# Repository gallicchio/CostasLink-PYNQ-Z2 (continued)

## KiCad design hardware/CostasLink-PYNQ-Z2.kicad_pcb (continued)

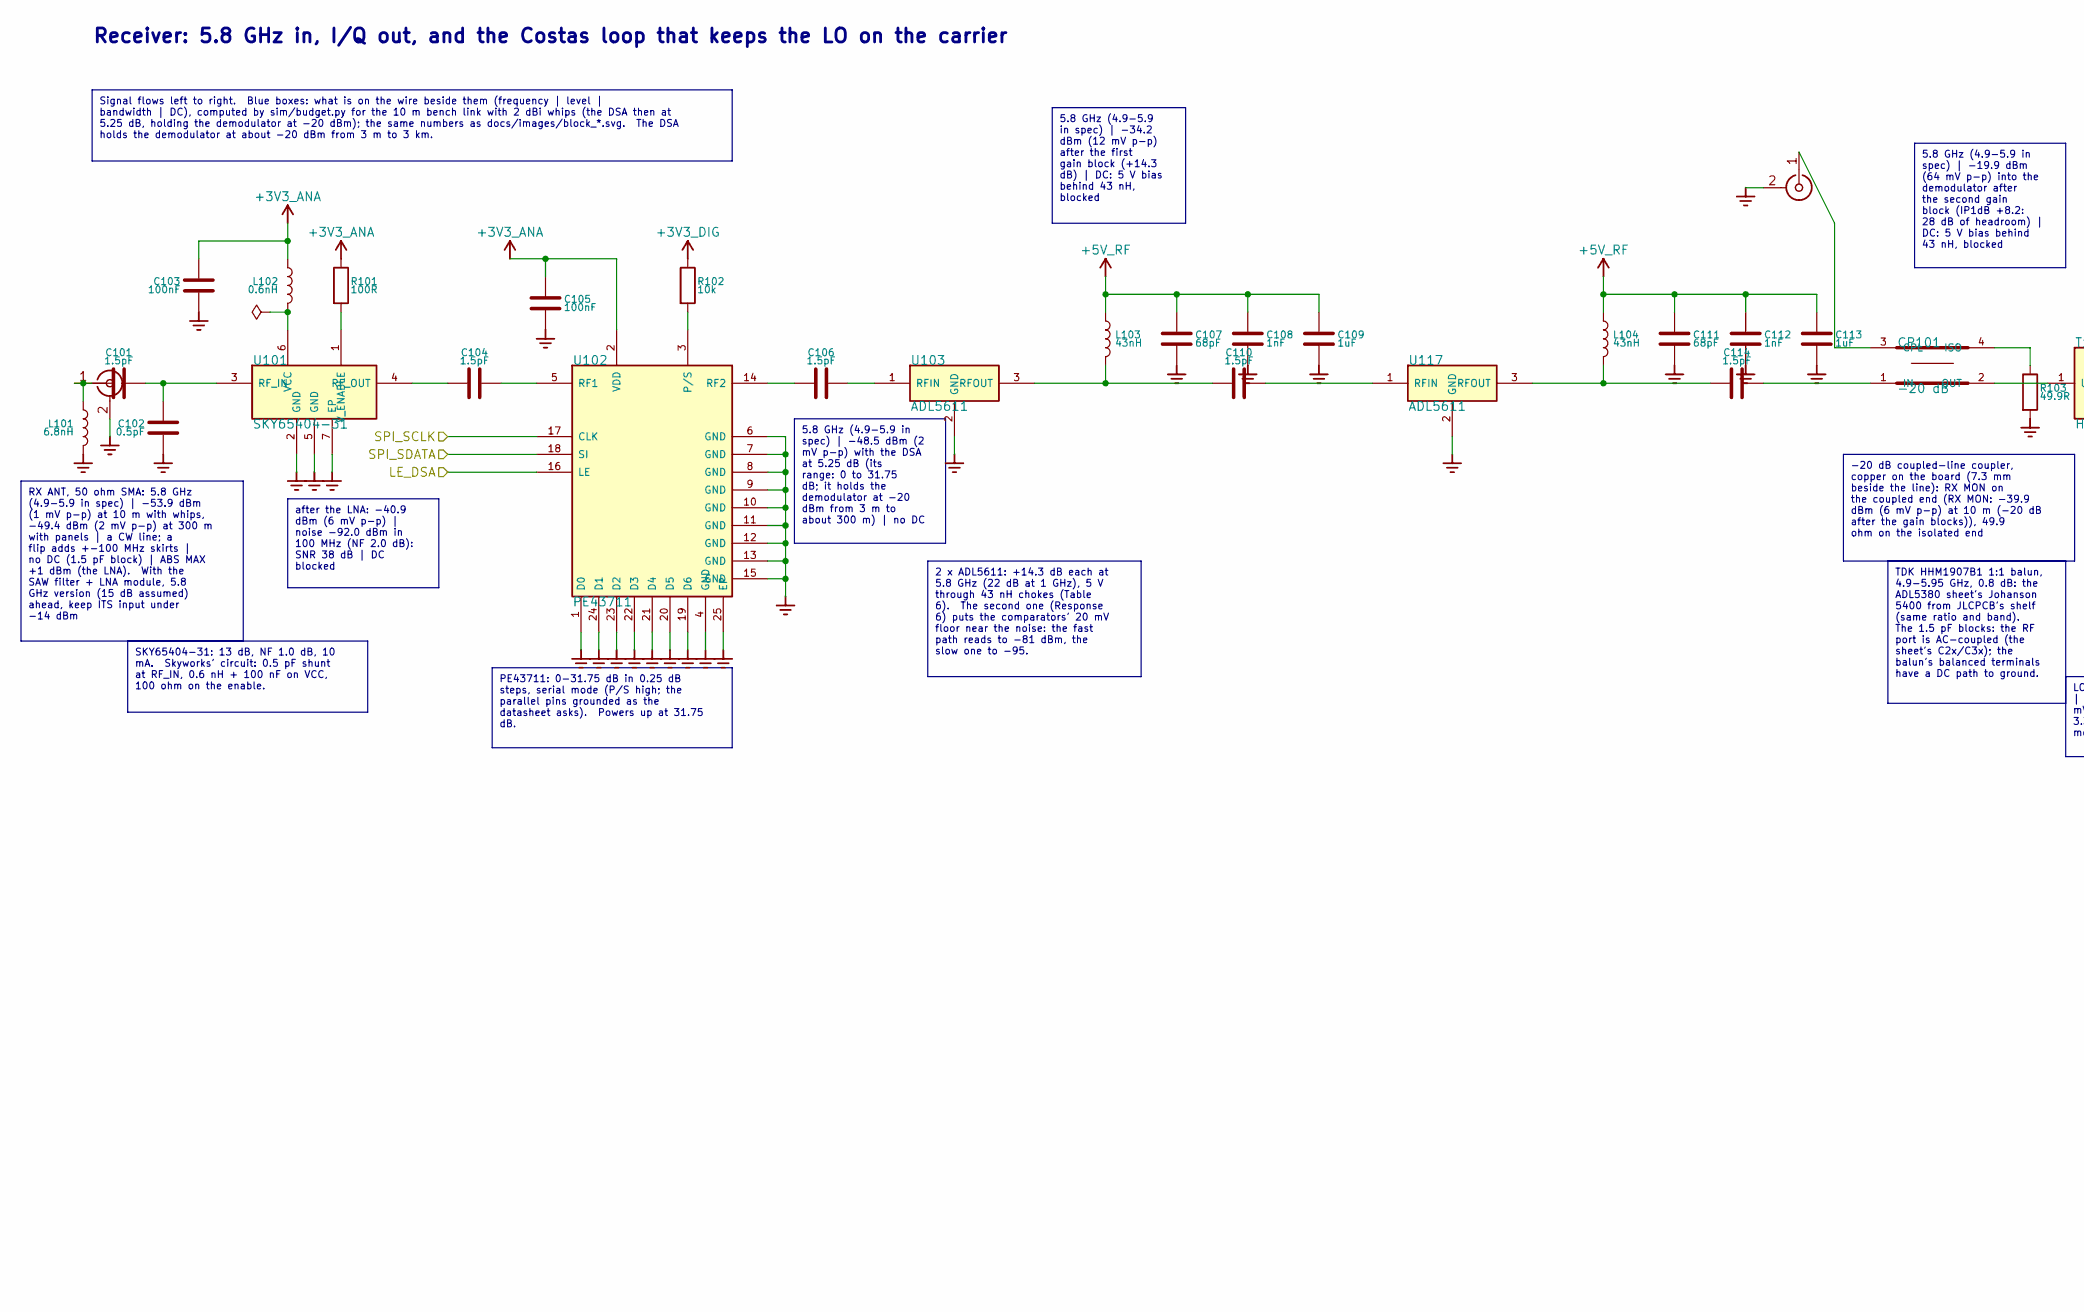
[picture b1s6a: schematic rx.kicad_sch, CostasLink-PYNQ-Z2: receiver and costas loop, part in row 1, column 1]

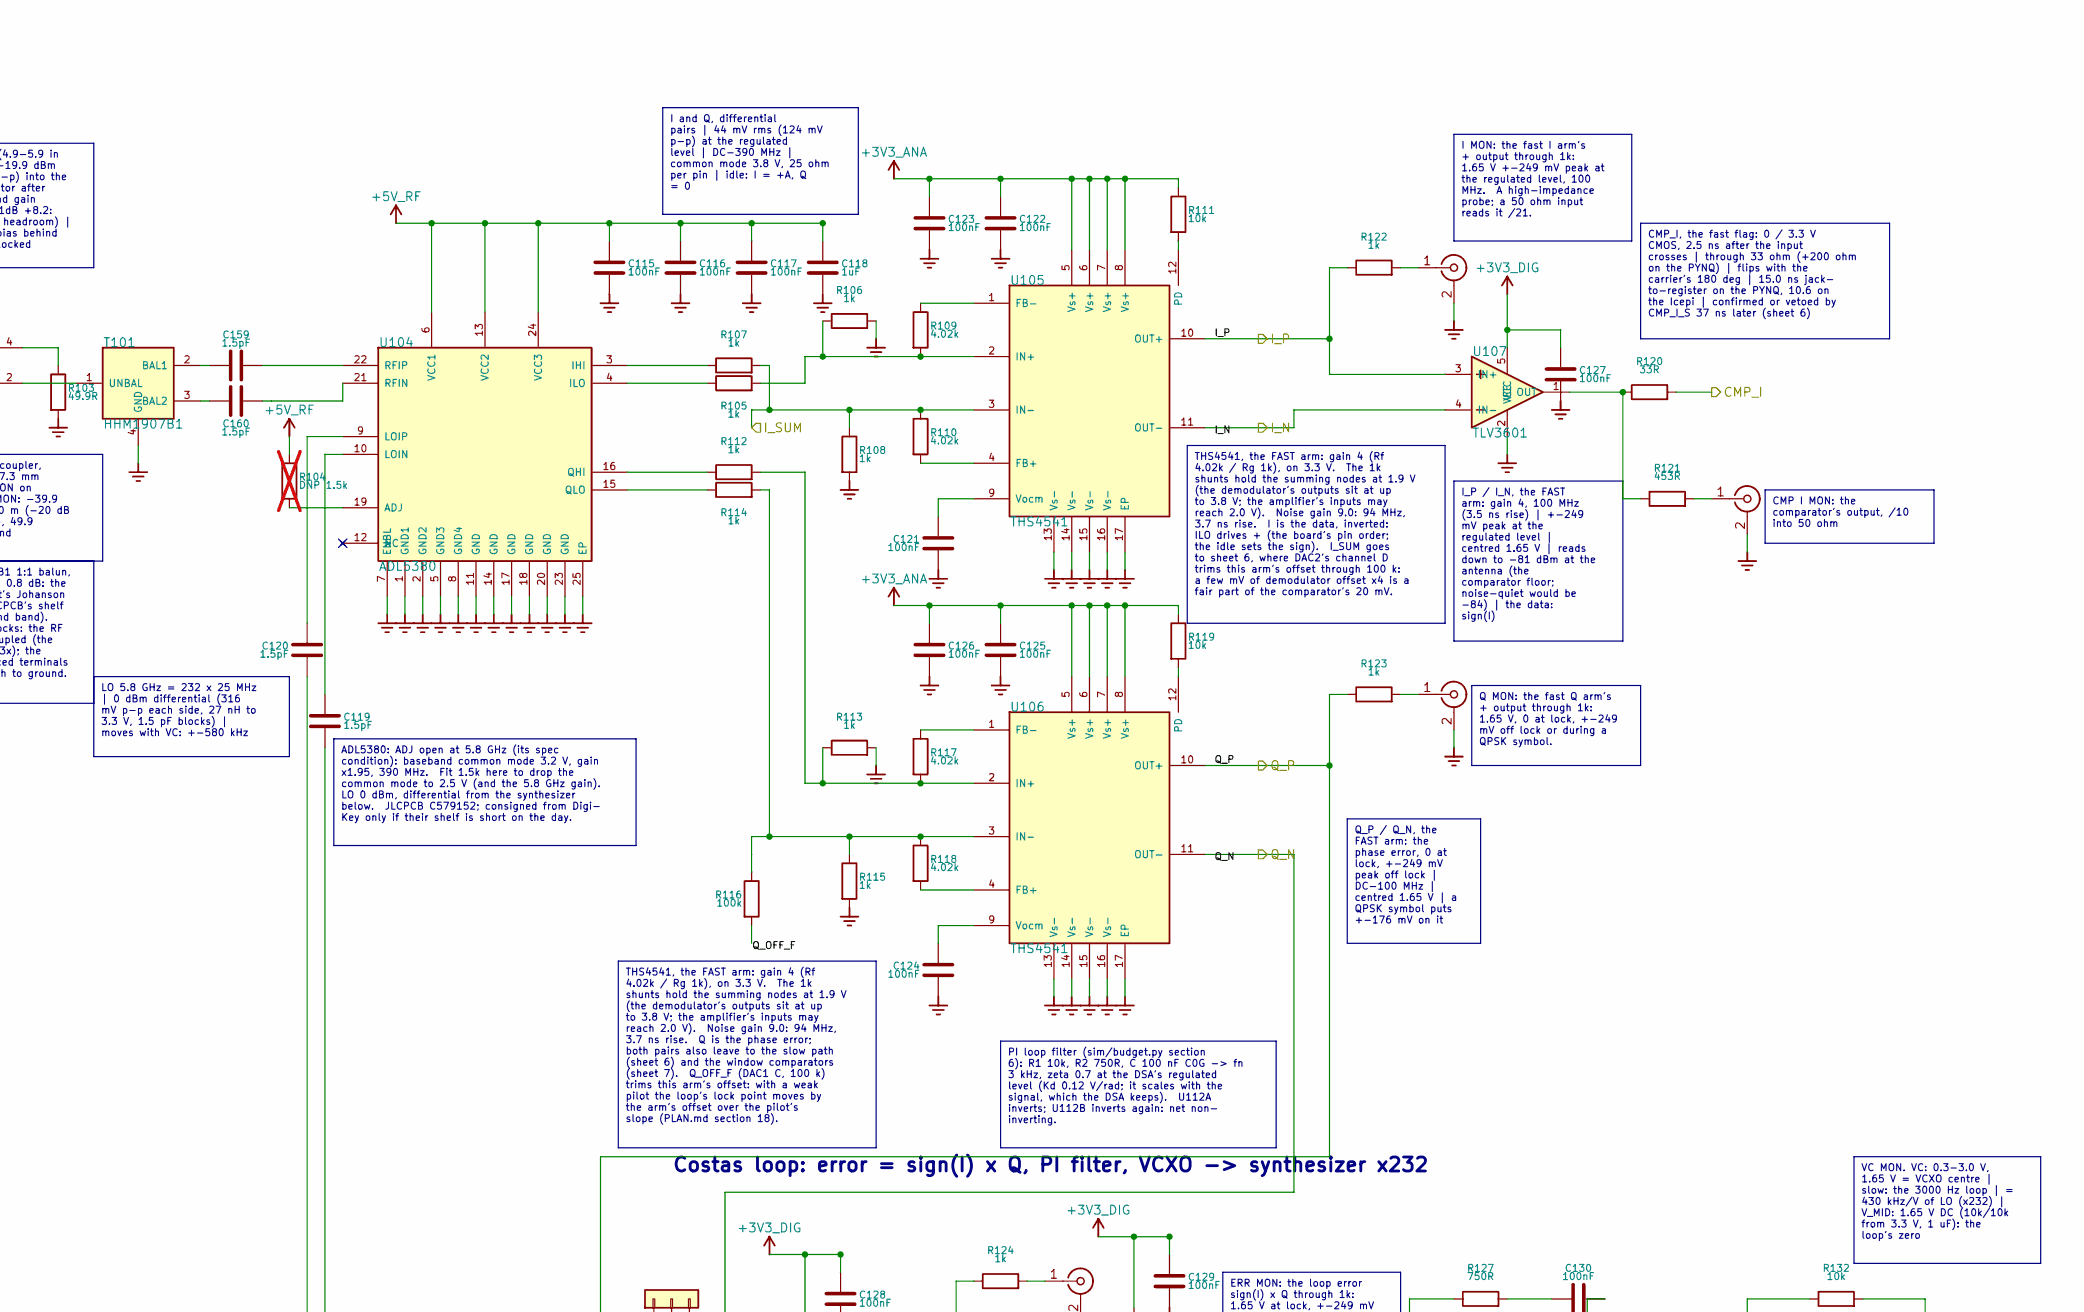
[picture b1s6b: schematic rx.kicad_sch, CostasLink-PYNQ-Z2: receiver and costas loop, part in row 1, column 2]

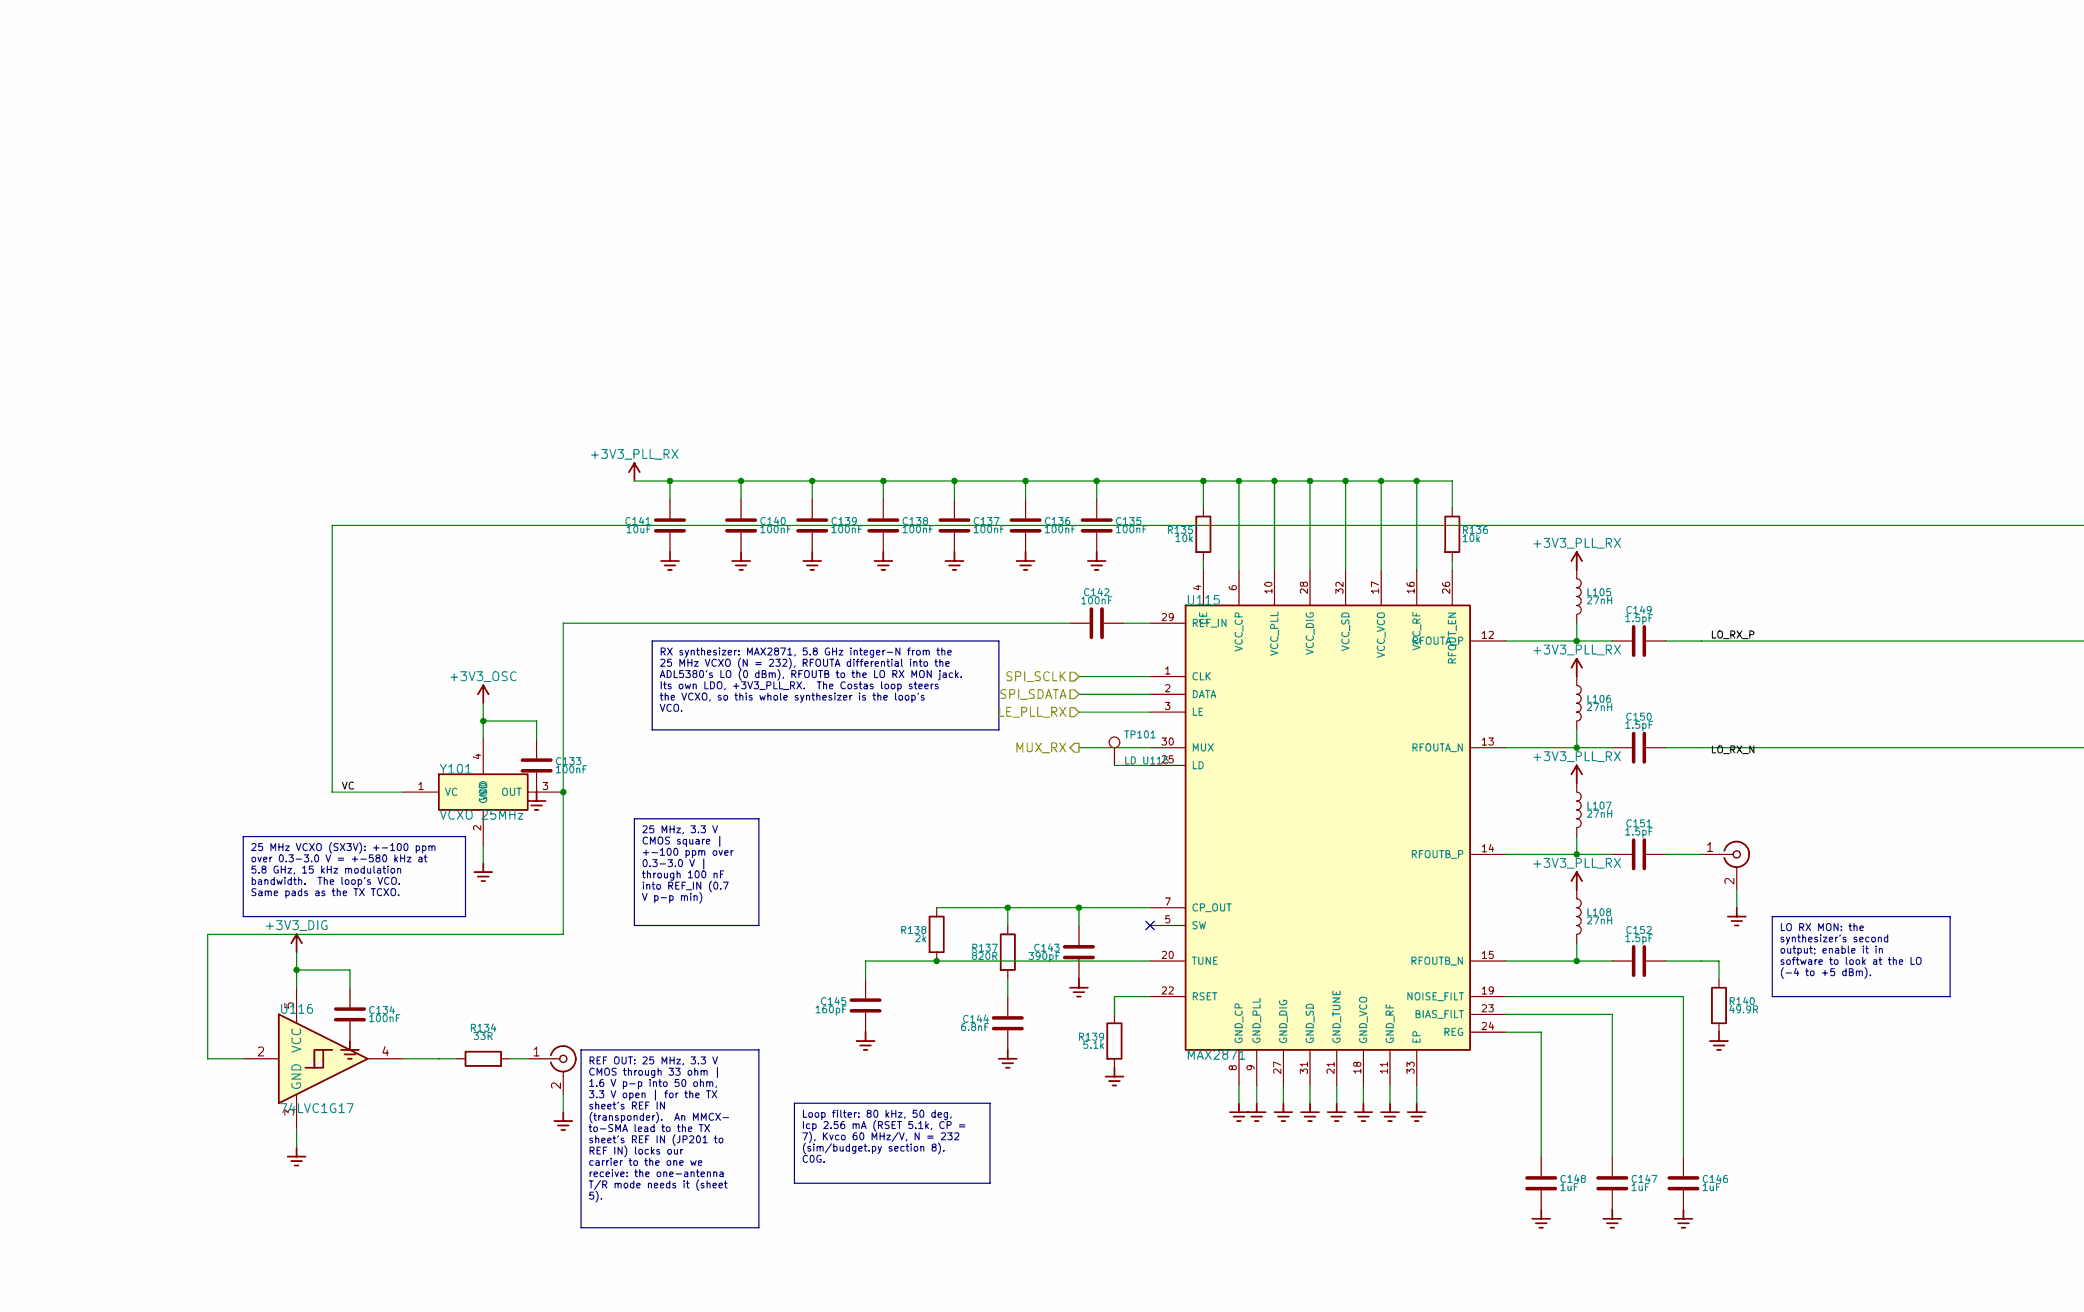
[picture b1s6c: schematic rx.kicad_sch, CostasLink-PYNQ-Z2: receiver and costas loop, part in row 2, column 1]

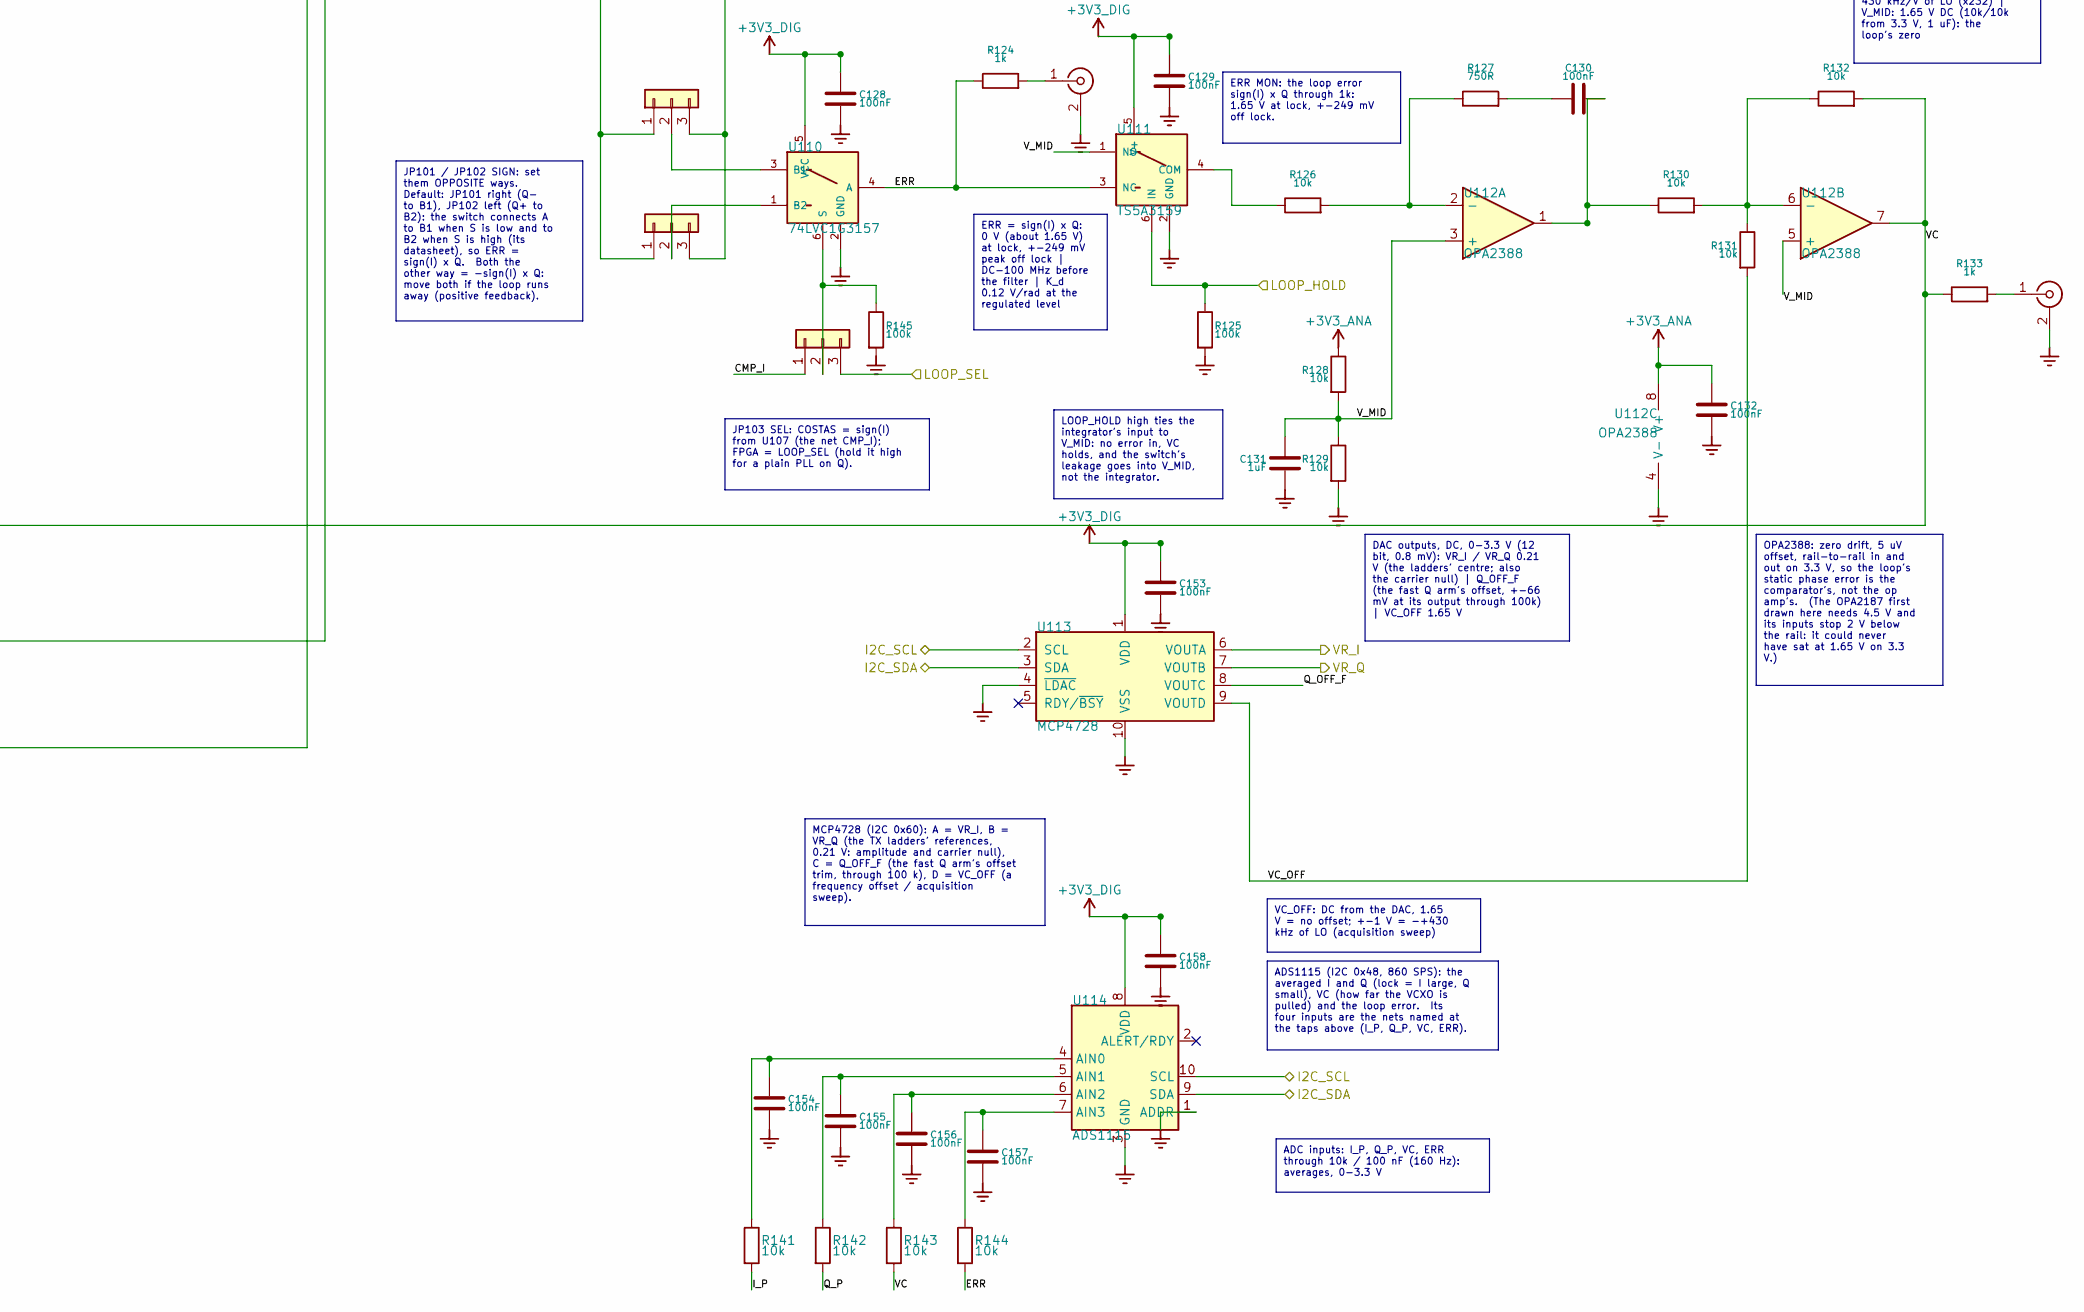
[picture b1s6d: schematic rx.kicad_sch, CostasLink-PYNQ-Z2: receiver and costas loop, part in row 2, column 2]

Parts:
C101, C104, C106, C110, C114, C119, C120, C149, C150, C151, C152, C159, C160: 1.5pF; C_0402_1005Metric; MPN 0402CG1R5C500NT; LCSC C1552
C102: 0.5pF; C_0402_1005Metric; MPN 0402CG0R5B500NT; LCSC C285052
C103, C105, C115, C116, C117, C121, C122, C123, C124, C125, C126, C127, C128, C129, C132, C133, C134, C135, C136, C137, C138, C139, C140, C142, C153, C154, C155, C156, C157, C158: 100nF; C_0402_1005Metric; MPN CL05B104KO5NNNC; LCSC C1525
C107, C111: 68pF; C_0402_1005Metric; MPN CL05C680JB5NNNC; LCSC C14441
C108, C112: 1nF; C_0402_1005Metric; MPN 0402B102K500NT; LCSC C1523
C109, C113, C118, C131, C146, C147, C148: 1uF; C_0402_1005Metric; MPN CL05A105KA5NQNC; LCSC C52923
C130: 100nF; C_1206_3216Metric; MPN 1206N104J500CT; LCSC C170182
C141: 10uF; C_0805_2012Metric; MPN CL21A106KAYNNNE; LCSC C15850
C143: 390pF; C_0402_1005Metric; MPN CC0402JRNPO9BN391; LCSC C282239
C144: 6.8nF; C_0603_1608Metric; MPN GRM1885C1H682JA01D; LCSC C162241
C145: 160pF; C_0402_1005Metric; MPN GCM1555C1H161JA16D; LCSC C2188753
CP101: -20 dB; Coupler_20dB_5.8GHz_CPWG
J101: RX ANT; SMA_BWSMA-KWE-Z001; MPN BWSMA-KWE-Z001; LCSC C496551
J102: RX MON; U.FL_Hirose_U.FL-R-SMT-1_Vertical; MPN U.FL-R-SMT-1(80); LCSC C88374
J103: CMP I MON; U.FL_Hirose_U.FL-R-SMT-1_Vertical; MPN U.FL-R-SMT-1(80); LCSC C88374
J104: I MON; U.FL_Hirose_U.FL-R-SMT-1_Vertical; MPN U.FL-R-SMT-1(80); LCSC C88374
J105: Q MON; U.FL_Hirose_U.FL-R-SMT-1_Vertical; MPN U.FL-R-SMT-1(80); LCSC C88374
J106: ERR MON; MMCX_BWMMCX-KE_Vertical; MPN BWMMCX-KE; LCSC C5137198
J107: VC MON; MMCX_BWMMCX-KE_Vertical; MPN BWMMCX-KE; LCSC C5137198
J108: REF OUT; MMCX_BWMMCX-KE_Vertical; MPN BWMMCX-KE; LCSC C5137198
J109: LO RX MON; U.FL_Hirose_U.FL-R-SMT-1_Vertical; MPN U.FL-R-SMT-1(80); LCSC C88374
JP101, JP102: SIGN; PinHeader_1x03_P2.54mm_Vertical; MPN PZ254V-11-03P; LCSC C2937625
JP103: SEL; PinHeader_1x03_P2.54mm_Vertical; MPN PZ254V-11-03P; LCSC C2937625
L101: 6.8nH; L_0402_1005Metric; MPN LQW15AN6N8G00D; LCSC C82919
L102: 0.6nH; L_0402_1005Metric; MPN MLG1005S0N6CT000; LCSC C95042
L103, L104: 43nH; L_0603_1608Metric; MPN LQW18AN43NG00D; LCSC C113126
L105, L106, L107, L108: 27nH; L_0402_1005Metric; MPN LQW15AN27NG80D; LCSC C882469
R101: 100R; R_0402_1005Metric; MPN 0402WGF1000TCE; LCSC C25076
R102, R111, R119, R126, R128, R129, R130, R131, R132, R135, R136, R141, R142, R143, R144: 10k; R_0402_1005Metric; MPN 0402WGF1002TCE; LCSC C25744
R103, R140: 49.9R; R_0402_1005Metric; MPN 0402WGF499JTCE; LCSC C25120
R104: DNP 1.5k; R_0402_1005Metric; MPN 0402WGF1501TCE; LCSC C25867; not fitted
R105, R106, R107, R108, R112, R113, R114, R115, R122, R123, R124, R133: 1k; R_0402_1005Metric; MPN 0402WGF1001TCE; LCSC C11702
R109, R110, R117, R118: 4.02k; R_0402_1005Metric; MPN RC0402FR-074K02L; LCSC C137968
R116, R125, R145: 100k; R_0402_1005Metric; MPN 0402WGF1003TCE; LCSC C25741
R120, R134: 33R; R_0402_1005Metric; MPN 0402WGF330JTCE; LCSC C25105
R121: 453R; R_0402_1005Metric; MPN FRC0402F4530TS; LCSC C5126227
R127: 750R; R_0402_1005Metric; MPN 0402WGF7500TCE; LCSC C25132
R137: 820R; R_0402_1005Metric; MPN 0402WGF8200TCE; LCSC C25135
R138: 2k; R_0402_1005Metric; MPN 0402WGF2001TCE; LCSC C4109
R139: 5.1k; R_0402_1005Metric; MPN 0402WGF5101TCE; LCSC C25905
T101: HHM1907B1; Balun_TDK_HHM1907B1; MPN HHM1907B1; LCSC C531388
TP101: LD U115; TestPoint_Pad_D1.5mm
U101: SKY65404-31; SKY65404-31_QFN-6_1.5x1.5mm; MPN SKY65404-31; LCSC C210262
U102: PE43711; QFN-24-1EP_4x4mm_P0.5mm_EP2.6x2.6mm; MPN PE43711B-Z; LCSC C470929
U103, U117: ADL5611; SOT-89-3; MPN ADL5611ARKZ-R7; LCSC C208262
U104: ADL5380; QFN-24-1EP_4x4mm_P0.5mm_EP2.6x2.6mm; MPN ADL5380ACPZ-R7; LCSC C579152
U105, U106: THS4541; VQFN-16-1EP_3x3mm_P0.5mm_EP1.68x1.68mm; MPN THS4541IRGTT; LCSC C2058382
U107: TLV3601; SOT-353_SC-70-5; MPN TLV3601DCKR; LCSC C2974371
U110: 74LVC1G3157; SOT-363_SC-70-6; MPN SN74LVC1G3157DCKR; LCSC C38663
U111: TS5A3159; SOT-363_SC-70-6; MPN TS5A3159DCKR; LCSC C46388
U112: OPA2388; VSSOP-8_3x3mm_P0.65mm; MPN OPA2388IDGKR; LCSC C2059281
U113: MCP4728; MSOP-10_3x3mm_P0.5mm; MPN MCP4728T-E/UN; LCSC C478093
U114: ADS1115; TSSOP-10_3x3mm_P0.5mm; MPN ADS1115IDGSR; LCSC C37593
U115: MAX2871; QFN-32-1EP_5x5mm_P0.5mm_EP3.1x3.1mm; MPN MAX2871ETJ+T; LCSC C7458627
U116: 74LVC1G17; SOT-353_SC-70-5; MPN SN74LVC1G17DCKR; LCSC C10425
Y101: VCXO 25MHz; Crystal_SMD_3225-4Pin_3.2x2.5mm; MPN SX3V25.000B20100F30TNN; LCSC C5179998

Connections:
+3V3_ANA: C103.1, C105.1, C122.1, C123.1, C125.1, C126.1, C132.1, L102.1, R101.1, R111.1, R119.1, R128.1, U102.2 (VDD), U105.5 (Vs+), U105.6 (Vs+), U105.7 (Vs+), U105.8 (Vs+), U106.5 (Vs+), U106.6 (Vs+), U106.7 (Vs+), U106.8 (Vs+), U112.8 (V+); also elsewhere on the board
+3V3_DIG: C127.1, C128.1, C129.1, C134.1, C153.1, C158.1, R102.1, U107.5 (VCC), U110.5 (VCC), U111.5 (V+), U113.1 (VDD), U114.8 (VDD), U116.5 (VCC); also elsewhere on the board
+3V3_OSC: C133.1, Y101.4 (VDD); also elsewhere on the board
+3V3_PLL_RX: C135.1, C136.1, C137.1, C138.1, C139.1, C140.1, C141.1, L105.1, L106.1, L107.1, L108.1, R135.1, R136.1, U115.6 (VCC_CP), U115.10 (VCC_PLL), U115.16 (VCC_RF), U115.17 (VCC_VCO), U115.28 (VCC_DIG), U115.32 (VCC_SD); also elsewhere on the board
+5V_RF: C107.1, C108.1, C109.1, C111.1, C112.1, C113.1, C115.1, C116.1, C117.1, C118.1, L103.1, L104.1, R104.1, U104.6 (VCC1), U104.13 (VCC2), U104.24 (VCC3); also elsewhere on the board
/I2C_SCL: U113.2 (SCL), U114.10 (SCL); also elsewhere on the board
/I2C_SDA: U113.3 (SDA), U114.9 (SDA); also elsewhere on the board
/I_N: U105.11 (OUT-), U107.4 (IN-); also elsewhere on the board
/I_P: R122.1, R141.2, U105.10 (OUT+), U107.3 (IN+); also elsewhere on the board
/Power and FPGA header/LE_DSA: U102.16 (LE); also elsewhere on the board
/Power and FPGA header/LE_PLL_RX: U115.3 (LE); also elsewhere on the board
/Power and FPGA header/LOOP_HOLD: R125.1, U111.6 (IN); also elsewhere on the board
/Power and FPGA header/LOOP_SEL: JP103.3; also elsewhere on the board
/Power and FPGA header/MUX_RX: U115.30 (MUX); also elsewhere on the board
/Power and FPGA header/SPI_SCLK: U102.17 (CLK), U115.1 (CLK); also elsewhere on the board
/Power and FPGA header/SPI_SDATA: U102.18 (SI), U115.2 (DATA); also elsewhere on the board
/Q_N: JP101.3, JP102.3, U106.11 (OUT-); also elsewhere on the board
/Q_P: JP101.1, JP102.1, R123.1, R142.2, U106.10 (OUT+); also elsewhere on the board
/Receiver and Costas loop/CMP_I: JP103.1, R120.2; also elsewhere on the board
/Receiver and Costas loop/ERR: R124.1, R144.2, U110.4 (A), U111.3 (NC)
/Receiver and Costas loop/I_SUM: R107.2, R108.1, R110.1, U105.3 (IN-); also elsewhere on the board
/Receiver and Costas loop/LO_RX_N: C120.2, C150.2
/Receiver and Costas loop/LO_RX_P: C119.2, C149.2
/Receiver and Costas loop/Q_OFF_F: R116.2, U113.8 (VOUTC)
/Receiver and Costas loop/VC: R132.2, R133.1, R143.2, U112.7, Y101.1 (VC)
/Receiver and Costas loop/VC_OFF: R131.2, U113.9 (VOUTD)
/Receiver and Costas loop/VR_I: U113.6 (VOUTA); also elsewhere on the board
/Receiver and Costas loop/VR_Q: U113.7 (VOUTB); also elsewhere on the board
/Receiver and Costas loop/V_MID: C131.1, R128.2, R129.1, U111.1 (NO), U112.3 (+), U112.5 (+)
unnamed: C130.1, R127.2
unnamed: C130.2, R130.1, U112.1
unnamed: C144.1, R137.2
unnamed: C152.2, R140.1
unnamed: CP101.3 (CPL), J102.1 (In)
unnamed: C114.2, CP101.1 (IN)
unnamed: CP101.4 (ISO), R103.1
unnamed: CP101.2 (OUT), T101.1 (UNBAL)
unnamed: C101.1, J101.1 (In), L101.1
unnamed: J103.1 (In), R121.2
unnamed: J104.1 (In), R122.2
unnamed: J105.1 (In), R123.2
unnamed: J106.1 (In), R124.2
unnamed: J107.1 (In), R133.2
unnamed: J108.1 (In), R134.2
unnamed: C151.2, J109.1 (In)
unnamed: JP101.2, U110.3 (B1)
unnamed: JP102.2, U110.1 (B2)
unnamed: JP103.2, R145.1, U110.6 (S)
unnamed: R134.1, U116.4
unnamed: C159.1, T101.2 (BAL1)
unnamed: C160.1, T101.3 (BAL2)
unnamed: C101.2, C102.1, U101.3 (RF_IN)
unnamed: C104.1, U101.4 (RF_OUT)
unnamed: L102.2, U101.6 (VCC)
unnamed: R101.2, U101.1 (V_ENABLE)
unnamed: R102.2, U102.3 (P/S)
unnamed: C104.2, U102.5 (RF1)
unnamed: C106.1, U102.14 (RF2)
unnamed: C106.2, U103.1 (RFIN)
unnamed: C110.1, L103.2, U103.3 (RFOUT)
unnamed: R104.2, U104.19 (ADJ)
unnamed: R107.1, U104.3 (IHI)
unnamed: R105.1, U104.4 (ILO)
unnamed: C119.1, U104.10 (LOIN)
unnamed: C120.1, U104.9 (LOIP)
unnamed: R112.1, U104.16 (QHI)
unnamed: R114.1, U104.15 (QLO)
unnamed: C160.2, U104.21 (RFIN)
unnamed: C159.2, U104.22 (RFIP)
unnamed: R110.2, U105.4 (FB+)
unnamed: R109.1, U105.1 (FB-)
unnamed: R105.2, R106.1, R109.2, U105.2 (IN+)
unnamed: R111.2, U105.12 (PD)
unnamed: C121.1, U105.9 (Vocm)
unnamed: R118.2, U106.4 (FB+)
unnamed: R117.1, U106.1 (FB-)
unnamed: R112.2, R113.1, R117.2, U106.2 (IN+)
unnamed: R114.2, R115.1, R116.1, R118.1, U106.3 (IN-)
unnamed: R119.2, U106.12 (PD)
unnamed: C124.1, U106.9 (Vocm)
unnamed: R120.1, R121.1, U107.1 (OUT)
unnamed: R126.1, U111.4 (COM)
unnamed: R126.2, R127.1, U112.2 (-)
unnamed: R130.2, R131.1, R132.1, U112.6 (-)
unnamed: C154.1, R141.1, U114.4 (AIN0)
unnamed: C155.1, R142.1, U114.5 (AIN1)
unnamed: C156.1, R143.1, U114.6 (AIN2)
unnamed: C157.1, R144.1, U114.7 (AIN3)
unnamed: C147.1, U115.23 (BIAS_FILT)
unnamed: R135.2, U115.4 (CE)
unnamed: C143.1, R137.1, R138.1, U115.7 (CP_OUT)
unnamed: TP101.1, U115.25 (LD)
unnamed: C146.1, U115.19 (NOISE_FILT)
unnamed: C142.2, U115.29 (REF_IN)
unnamed: C148.1, U115.24 (REG)
unnamed: C150.1, L106.2, U115.13 (RFOUTA_N)
unnamed: C149.1, L105.2, U115.12 (RFOUTA_P)
unnamed: C152.1, L108.2, U115.15 (RFOUTB_N)
unnamed: C151.1, L107.2, U115.14 (RFOUTB_P)
unnamed: R136.2, U115.26 (RFOUT_EN)
unnamed: R139.1, U115.22 (RSET)
unnamed: C145.1, R138.2, U115.20 (TUNE)
unnamed: C110.2, U117.1 (RFIN)
unnamed: C114.1, L104.2, U117.3 (RFOUT)
unnamed: C142.1, U116.2, Y101.3 (OUT)

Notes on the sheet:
Receiver: 5.8 GHz in, I/Q out, and the Costas loop that keeps the LO on the carrier
Costas loop: error = sign(I) x Q, PI filter, VCXO -> synthesizer x232
Signal flows left to right. Blue boxes: what is on the wire beside them (frequency | level | bandwidth | DC), computed by sim/budget.py for the 10 m bench link with 2 dBi whips (the DSA then at 5.25 dB, holding the demodulator at -20 dBm); the same numbers as docs/images/block_*.svg. The DSA holds 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
RX ANT, 50 ohm SMA: 5.8 GHz (4.9-5.9 in spec) | -53.9 dBm (1 mV p-p) at 10 m with whips, -49.4 dBm (2 mV p-p) at 300 m with panels | a CW line; a flip adds +-100 MHz skirts | no DC (1.5 pF block) | ABS MAX +1 dBm (the LNA). With the SAW filter + LNA module, 5.8 GHz version (15 dB assumed) ahead, ke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
SKY65404-31: 13 dB, NF 1.0 dB, 10 mA. Skyworks' circuit: 0.5 pF shunt at RF_IN, 0.6 nH + 100 nF on VCC, 100 ohm on the enable.
after the LNA: -40.9 dBm (6 mV p-p) | noise -92.0 dBm in 100 MHz (NF 2.0 dB): SNR 38 dB | DC blocked
PE43711: 0-31.75 dB in 0.25 dB steps, serial mode (P/S high; the parallel pins grounded as the datasheet asks). Powers up at 31.75 dB.
5.8 GHz (4.9-5.9 in spec) | -48.5 dBm (2 mV p-p) with the DSA at 5.25 dB (its range: 0 to 31.75 dB; it holds the demodulator at -20 dBm from 3 m to about 300 m) | no DC
2 x ADL5611: +14.3 dB each at 5.8 GHz (22 dB at 1 GHz), 5 V through 43 nH chokes (Table 6). The second one (Response 6) puts the comparators' 20 mV floor near the noise: the fast path reads to -81 dBm, the slow one to -95.
5.8 GHz (4.9-5.9 in spec) | -34.2 dBm (12 mV p-p) after the first gain block (+14.3 dB) | DC: 5 V bias behind 43 nH, blocked
-20 dB coupled-line coupler, copper on the board (7.3 mm beside the line): RX MON on the coupled end (RX MON: -39.9 dBm (6 mV p-p) at 10 m (-20 dB after the gain blocks)), 49.9 ohm on the isolated end
5.8 GHz (4.9-5.9 in spec) | -19.9 dBm (64 mV p-p) into the demodulator after the second gain block (IP1dB +8.2: 28 dB of headroom) | DC: 5 V bias behind 43 nH, blocked
TDK HHM1907B1 1:1 balun, 4.9-5.95 GHz, 0.8 dB: the ADL5380 sheet's Johanson 5400 from JLCPCB's shelf (same ratio and band). The 1.5 pF blocks: the RF port is AC-coupled (the sheet's C2x/C3x); the balun's balanced terminals have a DC path to ground.
ADL5380: ADJ open at 5.8 GHz (its spec condition): baseband common mode 3.2 V, gain x1.95, 390 MHz. Fit 1.5k here to drop the common mode to 2.5 V (and the 5.8 GHz gain). LO 0 dBm, differential from the synthesizer below. JLCPCB C579152; consigned from Digi- Key only if their shelf is short on the 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
LO 5.8 GHz = 232 x 25 MHz | 0 dBm differential (316 mV p-p each side, 27 nH to 3.3 V, 1.5 pF blocks) | moves with VC: +-580 kHz
THS4541, the FAST arm: gain 4 (Rf 4.02k / Rg 1k), on 3.3 V. The 1k shunts hold the summing nodes at 1.9 V (the demodulator's outputs sit at up to 3.8 V; the amplifier's inputs may reach 2.0 V). Noise gain 9.0: 94 MHz, 3.7 ns rise. I is the data, inverted: ILO drives + (the board's pin order; the id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
I and Q, differential pairs | 44 mV rms (124 mV p-p) at the regulated level | DC-390 MHz | common mode 3.8 V, 25 ohm per pin | idle: I = +A, Q = 0
THS4541, the FAST arm: gain 4 (Rf 4.02k / Rg 1k), on 3.3 V. The 1k shunts hold the summing nodes at 1.9 V (the demodulator's outputs sit at up to 3.8 V; the amplifier's inputs may reach 2.0 V). Noise gain 9.0: 94 MHz, 3.7 ns rise. Q is the phase error; both pairs also leave to the slow path (sheet 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
CMP I MON: the comparator's output, /10 into 50 ohm
CMP_I, the fast flag: 0 / 3.3 V CMOS, 2.5 ns after the input crosses | through 33 ohm (+200 ohm on the PYNQ) | flips with the carrier's 180 deg | 15.0 ns jack- to-register on the PYNQ, 10.6 on the Icepi | confirmed or vetoed by CMP_I_S 37 ns later (sheet 6)
I_P / I_N, the FAST arm: gain 4, 100 MHz (3.5 ns rise) | +-249 mV peak at the regulated level | centred 1.65 V | reads down to -81 dBm at the antenna (the comparator floor; noise-quiet would be -84) | the data: sign(I)
I MON: the fast I arm's + output through 1k: 1.65 V +-249 mV peak at the regulated level, 100 MHz. A high-impedance probe; a 50 ohm input reads it /21.
Q MON: the fast Q arm's + output through 1k: 1.65 V, 0 at lock, +-249 mV off lock or during a QPSK symbol.
Q_P / Q_N, the FAST arm: the phase error, 0 at lock, +-249 mV peak off lock | DC-100 MHz | centred 1.65 V | a QPSK symbol puts +-176 mV on it
JP101 / JP102 SIGN: set them OPPOSITE ways. Default: JP101 right (Q- to B1), JP102 left (Q+ to B2): the switch connects A to B1 when S is low and to B2 when S is high (its datasheet), so ERR = sign(I) x Q. Both the other way = -sign(I) x Q: move both if the loop runs away (positive feedback).
JP103 SEL: COSTAS = sign(I) from U107 (the net CMP_I); FPGA = LOOP_SEL (hold it high for a plain PLL on Q).
ERR = sign(I) x Q: 0 V (about 1.65 V) at lock, +-249 mV peak off lock | DC-100 MHz before the filter | K_d 0.12 V/rad at the regulated level
ERR MON: the loop error sign(I) x Q through 1k: 1.65 V at lock, +-249 mV off lock.
LOOP_HOLD high ties the integrator's input to V_MID: no error in, VC holds, and the switch's leakage goes into V_MID, not the integrator.
PI loop filter (sim/budget.py section 6): R1 10k, R2 750R, C 100 nF C0G -> fn 3 kHz, zeta 0.7 at the DSA's regulated level (Kd 0.12 V/rad; it scales with the signal, which the DSA keeps). U112A inverts; U112B inverts again: net non- inverting.
VC MON. VC: 0.3-3.0 V, 1.65 V = VCXO centre | slow: the 3000 Hz loop | = 430 kHz/V of LO (x232) | V_MID: 1.65 V DC (10k/10k from 3.3 V, 1 uF): the loop's zero
OPA2388: zero drift, 5 uV offset, rail-to-rail in and out on 3.3 V, so the loop's static phase error is the comparator's, not the op amp's. (The OPA2187 first drawn here needs 4.5 V and its inputs stop 2 V below the rail: it could never have sat at 1.65 V on 3.3 V.)
25 MHz VCXO (SX3V): +-100 ppm over 0.3-3.0 V = +-580 kHz at 5.8 GHz, 15 kHz modulation bandwidth. The loop's VCO. Same pads as the TX TCXO.
25 MHz, 3.3 V CMOS square | +-100 ppm over 0.3-3.0 V | through 100 nF into REF_IN (0.7 V p-p min)
REF OUT: 25 MHz, 3.3 V CMOS through 33 ohm | 1.6 V p-p into 50 ohm, 3.3 V open | for the TX sheet's REF IN (transponder). An MMCX- to-SMA lead to the TX sheet's REF IN (JP201 to REF IN) locks our carrier to the one we receive: the one-antenna T/R mode needs it (sheet 5).
Loop filter: 80 kHz, 50 deg, Icp 2.56 mA (RSET 5.1k, CP = 7), Kvco 60 MHz/V, N = 232 (sim/budget.py section 8). C0G.
LO RX MON: the synthesizer's second output; enable it in software to look at the LO (-4 to +5 dBm).
RX synthesizer: MAX2871, 5.8 GHz integer-N from the 25 MHz VCXO (N = 232), RFOUTA differential into the ADL5380's LO (0 dBm), RFOUTB to the LO RX MON jack. Its own LDO, +3V3_PLL_RX. The Costas loop steers the VCXO, so this whole synthesizer is the loop's VCO.
VC_OFF: DC from the DAC, 1.65 V = no offset; +-1 V = -+430 kHz of LO (acquisition sweep)
DAC outputs, DC, 0-3.3 V (12 bit, 0.8 mV): VR_I / VR_Q 0.21 V (the ladders' centre; also the carrier null) | Q_OFF_F (the fast Q arm's offset, +-66 mV at its output through 100k) | VC_OFF 1.65 V
